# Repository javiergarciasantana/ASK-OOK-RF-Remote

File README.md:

# ASK-OOK-RF-Remote
Design files for my 433MHz RF remote specifically made to fit into VW Transporter T5/ Golf MK6 2 Button key fob casing.

## Introduction

The *"key"* to this project is to make a functional all-in-one remote key-fob for my VW Polo 6n2. My car came from factory with a key-fob (6N0837219AC) which only had a button for a light to help you find the door or ignition lock. Said key looked like this:

Additionally, my car came with a 3rd party alarm system installed from the dealer which I assume used a 433MHz additional remote with a rolling code protocol.

Nonetheless my car only had the spare key (without the light bulb) and the old alarm control unit installed behind the driver's side headlight (non UK car). Since I did not have the knowledge or expertise at the time of buying my Polo 2nd hand (I was 18), instead of getting another remote made from the existing unit, I decided to go the cheap route and buy the Aliexpress special, a 433Mhz ASK/OOK single code receiver with 2 remotes for 7EUR. [Link to the product](https://es.aliexpress.com/item/32966630703.html?spm=a2g0o.order_list.order_list_main.345.2b2e180265tnwY&gatewayAdapt=glo2esp)

At the time it seemed like the right choice since I wanted nothing to do with locking and unlocking my car manually (peasant things). And for a long time it was, however the first problem I noticed is that the quality of the remotes was awful, the switches degraded like crazy and I understood later that using the same single code protocol as the garage doors was not ideal. 

The remote issue I solved by getting another kind of separate remote and to this day it works like a charm after 3 years. Also and on another note, one of the best things about the receiver is that you can pair new remotes on the fly just by pressing the pairing button next to the 13 pin connector.

[Link to the other kind of remote
](https://es.aliexpress.com/item/1005008790564347.html?spm=a2g0o.productlist.main.8.6fdbm5GMm5GM2U&aem_p4p_detail=2026080811291710916937976636560000125169&algo_pvid=d8578ccd-89f3-46d1-b1c1-b2fdf87a9af6&algo_exp_id=d8578ccd-89f3-46d1-b1c1-b2fdf87a9af6-7&pdp_ext_f=%7B%22order%22%3A%2270%22%2C%22eval%22%3A%221%22%2C%22fromPage%22%3A%22search%22%7D&pdp_npi=6%40dis%21EUR%216.59%216.59%21%21%2150.04%2150.04%21%400b8848bf17862137573062011e0e0e%2112000046675551470%21sea%21ES%211662762699%21ACX%211%210%21n_tag%3A-29919%3Bd%3Aed28c003%3Bm03_new_user%3A-29894&curPageLogUid=M3C2liQSV3zS&utparam-url=scene%3Asearch%7Cquery_from%3A%7Cx_object_id%3A1005008790564347%7C_p_origin_prod%3A&search_p4p_id=2026080811291710916937976636560000125169_2)<br>

---

### What problem does it solve?

Here is an image of my current key setup:

As you can see, it doesn't look half bad, however, since I am always carrying many things in my hand and other keys (plus the keychain and remote make noise everytime I hit a road bump), I wanted an all-in-one OEM+ solution. For this I started looking at Golf MK4, MK6 & MK7 remotes and decided to go with the MK6 one. I now is rather bland but its in the middle from being too futuristic(MK7) or too dingy(MK4). 

The good thing is that all remotes can share the same HU66 blade and fit on the same kind of cylinder lock, however the transponder is not the same!!! I had to install a new ID44 chip on my new key-fob. 

[Link to the 2 button Golf MK6 key-fob](https://es.aliexpress.com/item/1005005737683184.html?spm=a2g0o.order_list.order_list_main.17.595b1802jJVIsa&gatewayAdapt=glo2esp)

> [!IMPORTANT]
> MK4, MK5, MK6 and MK7 Golf use different transponders, going from the ID48 to the ID88

So I guess months of my life learning PCB design bit by bit would be worth it right? 
Well, for the time being I have to say yes, it was totally worth it and I learned so much in the process and got a Unique OEM+ key for my Polo out of it.

---

### Installation of the Chinese receiver
For those of you that are curious or need a wiring diagram of the OEM installation, here is a small tutorial of how I installed the receiver into my car.

#### OEM alarm 20 Pin Harness diagram

Now here I wont go much into detail, However I have to add this: the Chinese Receiver has to be put into a specific jumper configuration to be able to operate the central pneumatic system that the Polo comes standard with. Moreover, I made the mistake to not write down the wire colors but here they are detailed pin by pin:

It's not very detailed, but simply jumping the 12v with what I wanted to actuate worked, so the receiver is most likely just a big box of relays (11v in the case of the LED for some reason unknown to me).

---

Here is a connection diagram of the pins that I used on the receiver and OEM harness:

Some of them like the automatic windows did not work correctly (it was spamming like crazy). But opening and closing is a breeze and even all 6 indicators light up (one blink means close, 2 blinks is opened). 

Lastly, the OEM alarm interior light does not work with this receiver, maybe its to do with a voltage difference.

## OTP Encoding
Now to be honest, I could have designed another receiver box/module that was rolling code and could communicate and pair with Golf MK6 key-fobs, therefore integrating the automatic roll-down/up windows function or even the interior ventilation gimmick. However i was very interested in messing with this simple protocol as an RF begginer's project, so maybe in the future something like this can be made since I preserved the PCB that came with the MK6 remote.

### What is OTP Encoding?

**OTP** stands for **One-Time Programmable**. In the context of the encoder, it means the microchip contains an internal non-volatile memory layer that is permanently burned during manufacturing at the semiconductor factory with a fixed, unchangeable **20-bit identification code**.

Older RF encoders (like the classic PT2262) required 8 to 12 physical hardware pins connected to solder jumpers or DIP switches on your PCB so you could manually set a binary address. OTP encoding eliminates all of that physical configuration. Therefore, I chose the EV1527 encoder for this project as its footprint is very small and is readily available.

[EV1527 Datasheet
](./docs/EV1527.PDF)

---

### The 20-Bit Address & Possible Combinations

Every time you press a button on an EV1527 keyfob, the chip transmits a 24-bit frame:
* **20 Bits:** Factory-programmed unique address ID
* **4 Bits:** Data bits corresponding to the 4 button inputs ($K_0, K_1, K_2, K_3$)

#### Mathematical Combinations:
$$\text{Total Address Combinations} = 2^{20} = 1,048,576$$

With over 1 million unique code combinations, the probability of the keyfob sharing the exact same address code with another device nearby is roughly 1 in 1.05 million.

---

### Why OTP Encoding is the Best Choice for the Keyfob

* **Saves Board Space & Cost:** Eliminating DIP switches or solder jumper banks drastically shrinks the PCB area—allowing us to fit the EV1527 easily on the small board layout
* **Zero Serial Management During Assembly:** You don't have to program microcontrollers or keep track of serial numbers when soldering. Every EV1527 chip off the reel is guaranteed to have a different hardcoded address straight out of the box.
* **Universal Receiver Compatibility:** Modern RF receivers (learning-code receivers like the one I have) use a simple pairing button. You press "Learn" on the receiver, press your keyfob button once, and the receiver saves your unique 20-bit ID into its memory.

---

### No Crystal Needed: The Internal Oscillator & $R_{OSC}$

The EV1527 does not require a crystal oscillator, crystal load capacitors, or an external clock source.

* **Internal RC Oscillator:** The chip uses an integrated Resistor-Capacitor (RC) oscillator circuit on the silicon die.
* **Single Resistor Control:** To set the clock speed, you simply connect a single external resistor ($R_{OSC}$) between the `OSC` pin and `VCC` (typically $300\text{ k}\Omega$ to $430\text{ k}\Omega$, with $330\text{ k}\Omega$ being the standard for $433.92\text{ MHz}$ systems).
* **How It Works:** The resistance value of $R_{OSC}$ determines the charge/discharge rate of the internal oscillator, setting the timing pulse width ($T_w$) for the transmitted ASK radio signal.

## ASK/OOK Modulation

**ASK** stands for **Amplitude Shift Keying**, and **OOK** stands for **On-Off Keying**. OOK is the simplest form of ASK modulation used in low-power wireless communication.

* **How It Works:** Rather than shifting frequencies (like FM/FSK), OOK represents digital data by turning the radio transmitter **ON** and **OFF**:
  * **Binary '1' (Mark):** The transmitter turns ON and emits a full-power $433.92\text{ MHz}$ carrier wave.
  * **Binary '0' (Space):** The transmitter turns completely OFF, emitting zero radio power ($0\text{ V}$).
* **Why It Is Popular:** Because transmitting a '0' consumes virtually zero current, OOK is extremely power-efficient. Combined with low hardware complexity, it is the ideal choice for battery-powered keyfobs and garage door openers.

---

### Switching from SYN115 to CMT2110A

#### 1. The Initial Choice: SYN115
The SYN115 was initially selected because it is a widely recognized 433 MHz ASK transmitter IC. However, reviewing its datasheet revealed that it requires a significant number of external passive components to function, including crystal load capacitors, external biasing networks, and multi-stage tuning circuits, which inflates both component cost and PCB space requirements.

* **Datasheet:** [SYN115 Datasheet](./docs/SYN113-SYN115-datasheet-version-1-1-.0.pdf)

#### 2. The Solution: CMT2110A
To keep the keyfob layout compact ($37 \times 23.4\text{ mm}$), the design was shifted to the **CMT2110A**. Thanks to its high level of internal silicon integration (integrated crystal load caps, bias circuits, and internal EEPROM power control), the entire RF section requires only:

* **2 Inductors:** 
  * $L_1$ (DC supply choke)
  * $L_2$ (Series matching inductor)
* **3 Capacitors:** 
  * $C_0$ (Power decoupling filter)
  * $C_1$ (Series DC blocking capacitor)
  * $C_2$ (Shunt harmonic filter capacitor)
* **1 Quartz Crystal:** 
  * A standard 4-pin SMD $26\text{ MHz}$ crystal package (where 1 pin carries the active clock signal to the `XTAL` pin, while the remaining grounded pins provide internal shield grounding).

* **Datasheet:** [CMT2110A Datasheet](./docs/info-rf-cmt2110a-esr.pdf)

---

### Why is 433.92 MHz Used?

The $433.92\text{ MHz}$ frequency band is the dominant standard for short-range remote controls due to four key advantages:

1. **Unlicensed ISM Band:** $433.05\text{ MHz} - 434.79\text{ MHz}$ is designated worldwide as an Industrial, Scientific, and Medical (ISM) band. Devices operating under short-range, low-duty-cycle rules can transmit without requiring expensive FCC/CE user licenses.
2. **Superior Obstacle Penetration:** Sub-1 GHz signals ($433\text{ MHz}$) have longer wavelengths ($\approx 69\text{ cm}$) compared to $2.4\text{ GHz}$ (Wi-Fi/Bluetooth, $\approx 12\text{ cm}$). This allows $433\text{ MHz}$ signals to easily penetrate walls, plastic key shells, and human hands with minimal signal attenuation.
3. **Ultra-Low Battery Consumption:** At $433.92\text{ MHz}$, simple power amplifiers consume very little current ($\approx 10 - 20\text{ mA}$ during transmission), enabling years of operation on a single CR2032 coin cell.
4. **Ideal Antenna Physical Size:** A standard quarter-wave antenna at $433\text{ MHz}$ is roughly $17\text{ cm}$, which easily scales down into compact PCB trace loop antennas suitable for handheld keyfobs while maintaining reliable range ($30 - 100\text{ meters}$).

## Schema Design

Now this was perhaps one of the most challenging steps as I did not know anything about Kicad beforehand. I watched a couple videos after choosing all of my components and I was ready to go. I satarted placing symbolds, common GND and added some jumpers for the buttons, just in case, so that I can change the input in case my receiver expects a different data input (1000 instead of 0001 or 0100 instead of 0010). Which depends on what input you give power to (K0-K3).

Now since the remote requires a cr2032 holder, I added its symbol (I put is as Do not populate, this is explained in the PCB design chapter) as well as the components required by the datasheets (combination of 0402 and 0603 LED, resistors, capacitors and inductors and a 4 pin Crystal). 

The LED is required in order to know wether the remote is working or not, and I added it in the TDX-DATA line between the EV1527 and the CMT2110A

Lastly, according to the CMT2110A datasheet, the CLK pin must remain disconnected as its only used to access the embedded EEPROM and change the IC's operational frequency and other parameters

## PCB Design

This was perhaps the most stressful part, as placing the components correctly and designling an antena trace that will work on real life is very challenging
I started taking meassurements of the original board to know exactly where to place the switches and antenna components.

### Antenna design

To design an antenna, firstly we have to position these components correctly, according to the datasheet, capacitor C0 needs to be as close as possible to the RFO pin on the chip for better filtering. Now the antenna circuit by itself can look a bit complex but its really simple:

#### 1. Impedance Matching (Maximum Power Transfer)
The output pin of the IC (RFO) has a specific internal electrical impedance (often several hundred ohms). A compact PCB keyfob antenna has a completely different impedance (typically low and highly reactive, e.g., $10\ \Omega - 50\ \Omega$).If you connect the pin straight to the antenna, an impedance mismatch occurs: over 90% of the radio power reflects back into the chip instead of radiating into the air. The LC network ($L_2, C_2, C_1$) acts as an RF transformer to match the two impedances so maximum power enters the antenna.
#### 2. Harmonic Suppression (Filtering Noise)The Power Amplifier (PA) inside the chip operates like a high-speed switch. This generates the main $433.92\text{ MHz}$ signal along with unwanted square-wave harmonics at multiples of the frequency ($867.84\text{ MHz}$, $1.3\text{ GHz}$, etc.). The LC components form a low-pass filter that strips out these higher frequencies so the board complies with legal radio emission limits (CE/FCC).

#### 3. DC Power Feeding ($L_1$ Choke)The output transistor inside the CMT2110A requires DC voltage from the battery to operate. $L_1$ allows direct DC current from $V_{DD}$ to flow into the RFO pin while acting as a "wall" (high impedance) to $433.92\text{ MHz}$ RF, keeping the radio signal from leaking back into the battery line.

#### 4. DC Blocking ($C_2$)Capacitor $C_2$ sits in series right before the antenna trace. It allows $433.92\text{ MHz}$ AC radio waves to pass through to the antenna while stopping DC voltage from reaching the antenna trace, preventing short circuits if the antenna touches a grounded frame or case.

#### Antenna trace

The antenna circuit also needs a trace (or a coil). This one was designed using the **Quarter-Wave Monopole ($\lambda/4$) Rule**, adjusted for the **velocity factor** of the FR4 PCB substrate, and routed using a **Meander Line Antenna (MLA)** topology.

---

##### 1. Quarter-Wavelength ($\lambda/4$) Resonant Length
Antennas achieve optimum resonance when their physical length corresponds to one-quarter of the target RF wavelength ($\lambda/4$). 

At $433.92\text{ MHz}$, the wavelength in free space is calculated as:

$$\lambda = \frac{c}{f} = \frac{3 \times 10^8\text{ m/s}}{433.92 \times 10^6\text{ Hz}} \approx 691.4\text{ mm}$$

In open air, a standard quarter-wave antenna requires a total length of:

$$\text{Length}_{\text{air}} = \frac{691.4\text{ mm}}{4} \approx 172.8\text{ mm}$$

---

##### 2. PCB Velocity Factor Adjustment
Radio waves travel slower through an FR4 substrate ($\epsilon_r \approx 4.4$) than through open air. This effective dielectric loading introduces a **velocity factor** ($v_f \approx 0.70$), which reduces the physical trace length required to achieve $433.92\text{ MHz}$ resonance:

$$\text{Physical Trace Length} = 172.8\text{ mm} \times 0.70 \approx 120\text{ mm}$$

By designing a total trace path of **$120\text{ mm}$**, the trace electrically matches a full $172.8\text{ mm}$ quarter-wave antenna radiating in free space.

---

##### 3. Meander Line Antenna (MLA) Geometry
A straight $120\text{ mm}$ trace cannot fit across a compact $37 \times 23.4\text{ mm}$ keyfob board. 

To solve this, a **meander line pattern** (a serpentine topology consisting of 7 vertical $12\text{ mm}$ segments and 7 horizontal $3\text{ mm}$ turns) was used. This layout maintains the continuous **$120\text{ mm}$ electrical path length** needed for proper resonance while compressing the physical footprint into a small bounding box.

---

##### 4. Trace Width Selection ($1\text{ mm}$)
Unlike narrow $0.2\text{ mm}$ logic traces, a wider **$1\text{ mm}$ width** was chosen for the antenna trace for two specific reasons:

* **Lower RF Conduction Loss:** At $433.92\text{ MHz}$, high-frequency currents travel primarily on the outer surface layer of copper (*skin effect*). A wider $1\text{ mm}$ trace increases surface area, significantly reducing high-frequency resistive losses.
* **Broader Impedance Bandwidth:** Increasing trace width widens the resonant frequency band, preventing the keyfob from detuning when encapsulated inside a plastic key shell or touched by a user's hand.

##### 5. No copper fill on the back of the antenna

To prevent any interference with the signal, the antenna needs to be isolated, with as little components of signals close to it, so that no power gets harnessed from the signal.

## Breadboard Prototype

## Final Results

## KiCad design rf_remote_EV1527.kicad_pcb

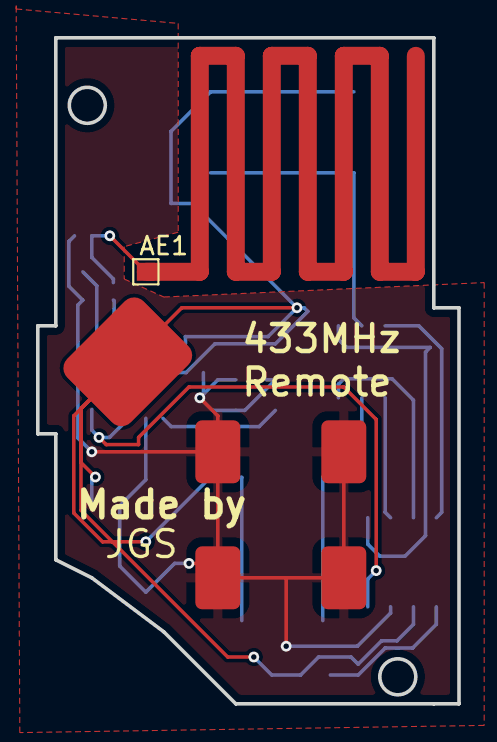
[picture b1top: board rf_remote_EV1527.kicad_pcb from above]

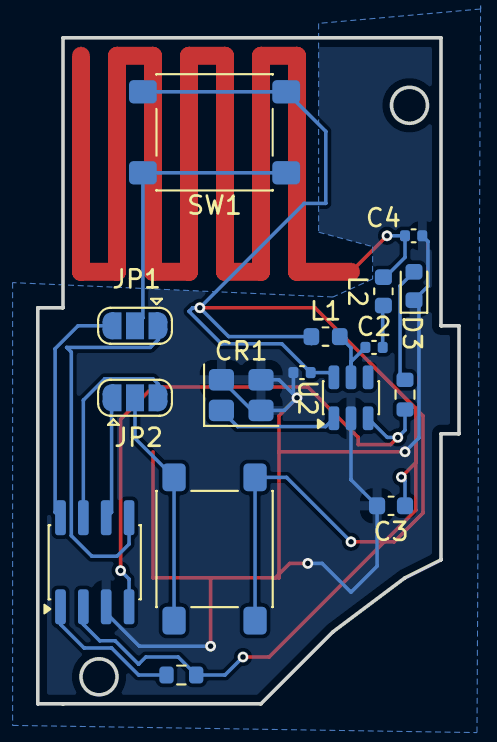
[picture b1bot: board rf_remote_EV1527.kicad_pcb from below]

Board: 2 copper layers, 23.4 x 37.0 mm, 18 parts (16 on the bottom side), 15 nets.

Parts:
AE1: Antenna; TestPoint_Pad_1.0x1.0mm
C1: 0.1uF; C_0402_1005Metric
C2: 82pF; C_0402_1005Metric
C3: 100NF; C_0603_1608Metric
C4: 9pF; C_0402_1005Metric
CR1: 26 MHz; Crystal_SMD_3225-4Pin_3.2x2.5mm
D3: LED; LED_0603_1608Metric
JP1, JP2: Jumper_3_Open; SolderJumper-3_P1.3mm_Open_RoundedPad1.0x1.5mm
L1: 180nH; L_0603_1608Metric
L2: 27nH; L_0603_1608Metric
R1: 330k; R_0603_1608Metric
R2: 1k; R_0603_1608Metric
SW1, SW2: SW_Push; SW_SPST_PTS645Sx43SMTR92
U1: EV1527; SOIC-8_3.9x4.9mm_P1.27mm
U2: CMT2110A; SOT-23-6
U3: CR2032; BatteryHolder_Keystone_3002_1x2032

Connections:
GND: C1.2, C3.2, C4.2, CR1.2, CR1.3, CR1.4, D3.1 (K), U1.3 (VSS), U2.2 (GND), U3.-
unnamed: AE1.1 (A), C4.1, L2.2
unnamed: C2.2, L2.1
unnamed: D3.2 (A), R2.1
unnamed: JP1.1 (A), U1.5 (K0)
unnamed: JP1.3 (B), U1.8 (K3)
unnamed: JP1.2 (C), SW1.1
unnamed: JP2.1 (A), U1.6 (K1)
unnamed: JP2.3 (B), U1.7 (K2)
unnamed: JP2.2 (C), SW2.1
unnamed: R1.2, U1.1 (OSC)
unnamed: R2.2, U1.4 (TXD), U2.3 (DATA)
unnamed: C1.1, C3.1, L1.1, R1.1, SW1.2, SW2.2, U1.2 (VCC), U2.6 (VDD), U3.+1
unnamed: C2.1, L1.2, U2.5 (RFO)
unnamed: CR1.1, U2.1 (XTAL)
